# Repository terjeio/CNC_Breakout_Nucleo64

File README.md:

## CNC Breakout board for Nucleo-64 based development boards using ST morpho extension header

[grblHAL driver](https://github.com/grblHAL/STM32F4xx) support for [Nucleo F411RE](https://www.st.com/en/evaluation-tools/nucleo-f411re.html) and [Nucleo F446RE](https://www.st.com/en/evaluation-tools/nucleo-f446re.html) development boards.

**NOTE:** design files are in [KiCad 5](http://www.kicad.org/) format!

**Features:**

* Four layer board

* 4-axis motor support with separate enable for all axes.

* On-board sockets for Polulu \(A4998 and DRV8825\) or Trinamic \(TMC2130 or TMC5160 - SPI mode, TMC2209 - UART mode\) style motor driver modules.

* Opto-coupled limit and signal inputs (X, Y, Z, A, Probe, Reset/E-Stop, Door, Feed Hold and Cycle Start).

* Opto-coupled signal outputs \(Spindle on, Spindle direction, Flood, Mist, Aux0 and Aux1\).
Outputs are open drain \(ULN2003\) capable of draining 500mA, enough to drive most relays directly.

* Jumper selectable drive voltage for inputs and outputs, either 5V internally supplied or 5-30V externally supplied. 
If externally supplied inputs and outputs can be made galvanically isolated from the controller via jumper settings.

* 5V buffered PWM output for spindle speed control.

* Optional optocoupled DC spindle output, can be made galvanically isolated via jumper setting. External supply voltage limited to rating of filtering capacitor C7 (max. 30V).

* I2C port with jumper selectable drive voltage \(3.3V or 5V\). This is complemented with a 5V tolerant input pin that may be used as an interrupt source, eg. for the strobe signal from a I2C-based keypad.

* Two GPIO ports, with two pins each. One is unbuffered and can be used for serial communincation, eg. for MPG or VFD control. One is input only and has 5V tolerant pins.

* Optional on-board EEPROM/FRAM for persistent storage of settings.

* SPI based SD-card interface. If not in use some or all pins may be used as GPIO or as a generic SPI interface with one chip select line, depending on motor drivers used.

---

I have a number of _bare_ boards available:

* 1.0 \(preliminary version\): 7 pcs. These do not support Trinamic drivers in SPI/UART mode and has a couple of correctable routing errors in the spindle PWM -> spindle DC circuit. Price: shipping at cost.

* 1.0b: 2 pcs. Price: EUR 5/pcs + shipping at cost. These are missing a pullup resistor for the keypad strobe input - this _may_ affect operation of the keypad plugin. Easy to add externally.

These boards are gold plated \(ENIG finish\).

* 1.0c: \(current version\) Not yet available.

I do not plan to offer populated boards as either I have to solder them myself \(will be expensive\) or place an order for ready made boards \(with only SMD components soldered\).  
A redesign is likely required for ready made boards as some of the components may not be available from the standard selection offered by e.g. [JLPCB](https://jlcpcb.com/).

It would be great if someone would get populated boards made and offered for sale as I am currently not prepared to do that.

---

2021-08-22

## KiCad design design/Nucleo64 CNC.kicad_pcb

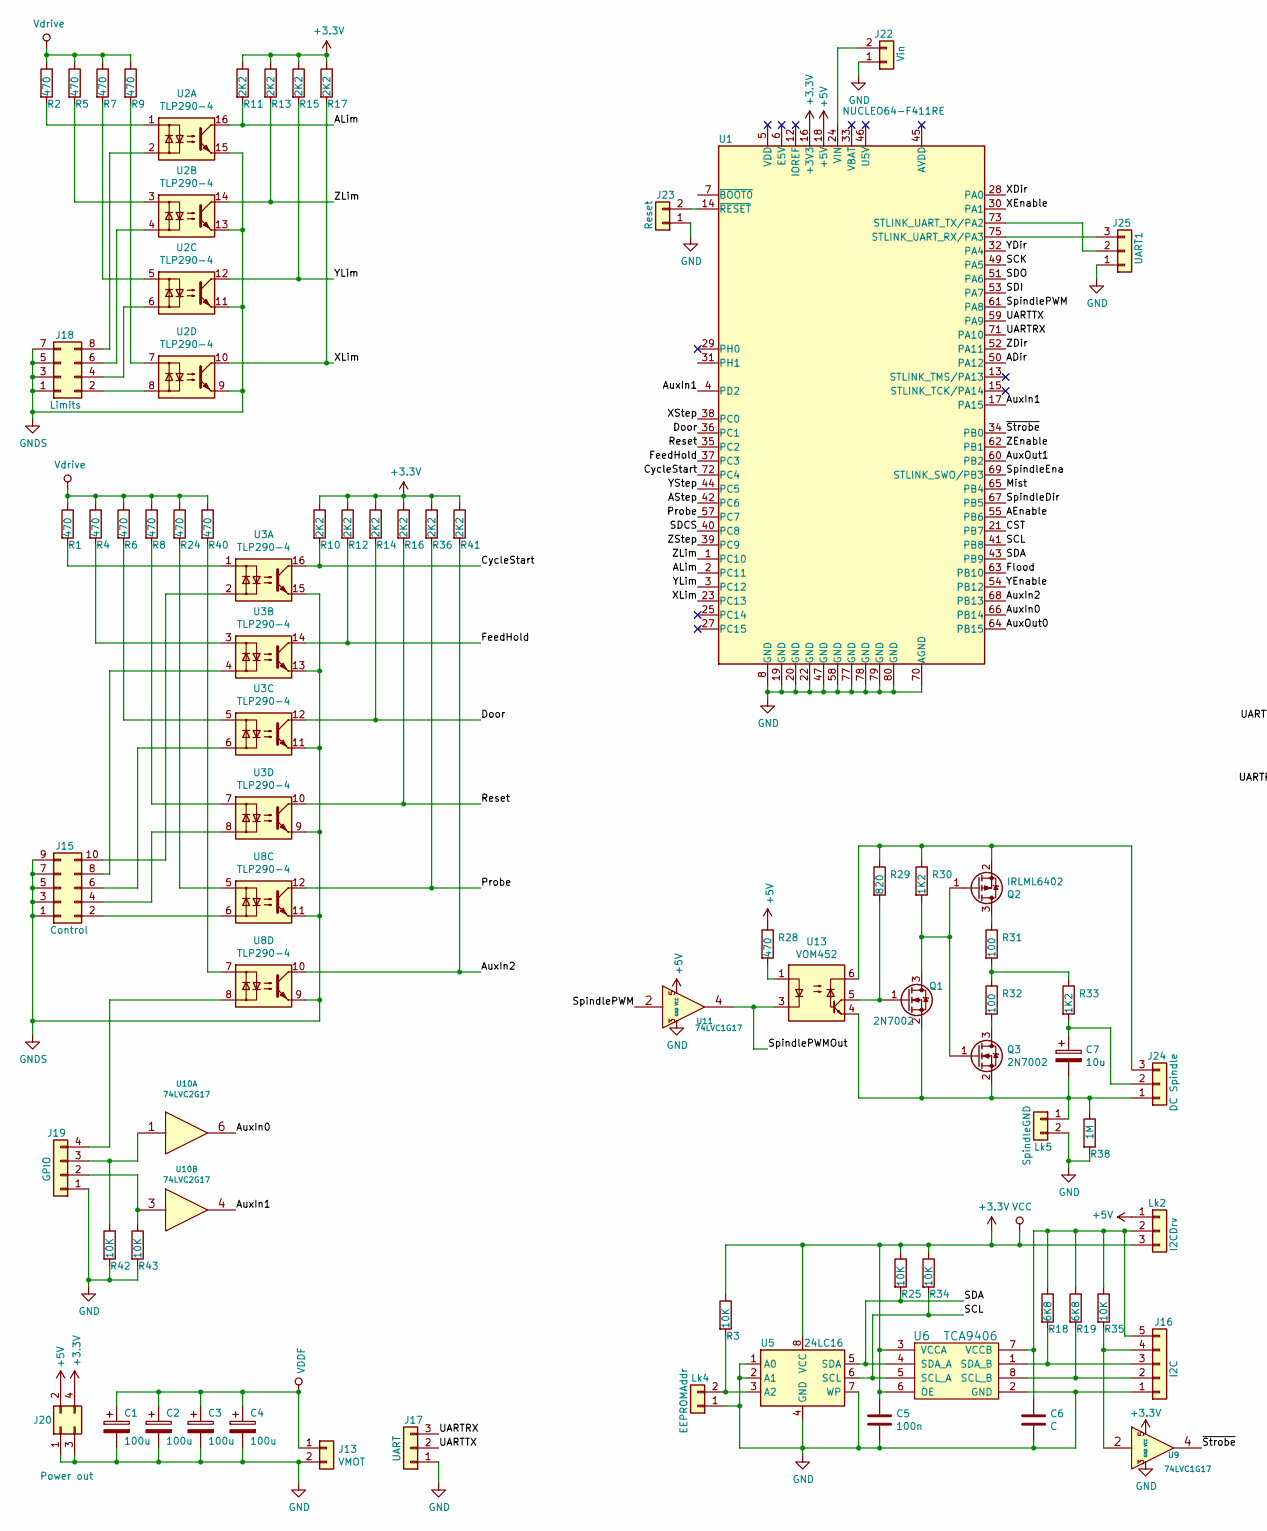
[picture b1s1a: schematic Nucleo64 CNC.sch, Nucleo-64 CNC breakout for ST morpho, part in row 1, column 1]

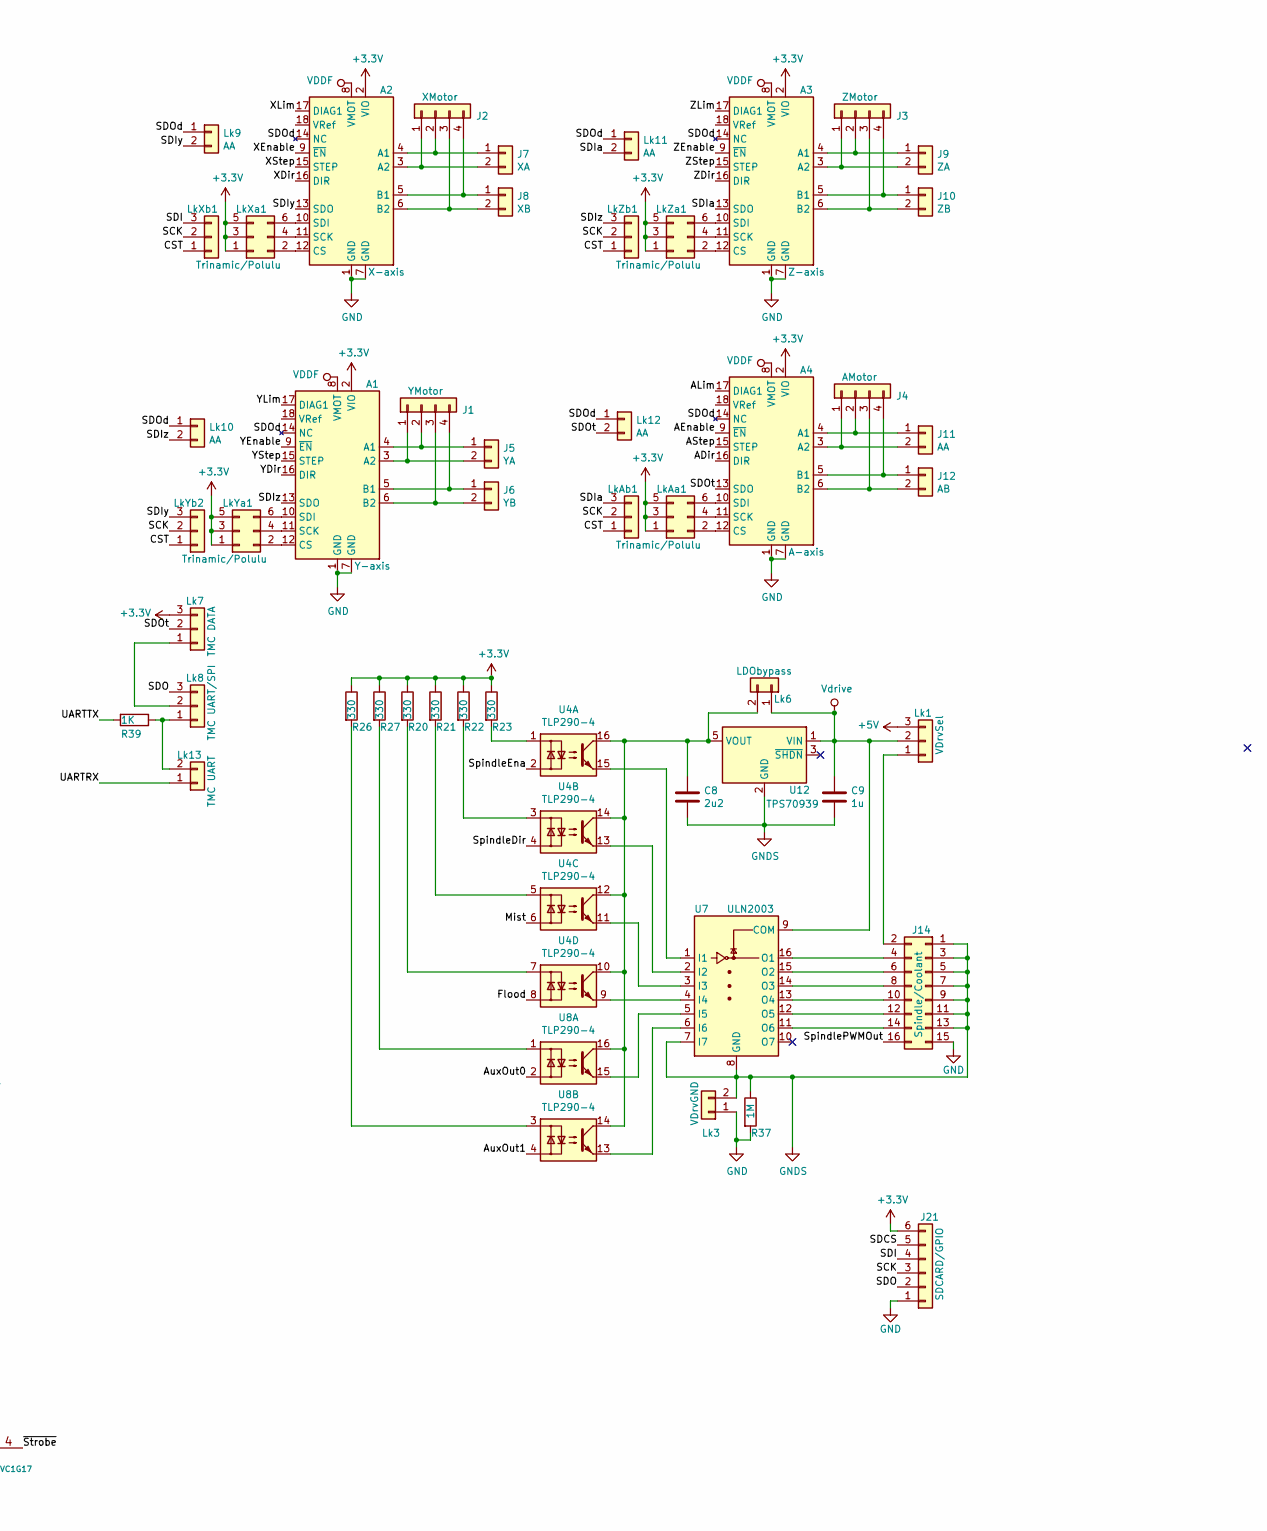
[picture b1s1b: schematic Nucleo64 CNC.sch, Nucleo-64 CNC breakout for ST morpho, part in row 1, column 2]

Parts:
A1: Y-axis; SilentStepStick_TMC2130
A2: X-axis; SilentStepStick_TMC2130
A3: Z-axis; SilentStepStick_TMC2130
A4: A-axis; SilentStepStick_TMC2130
C1, C2, C3, C4: 100u; CP_Radial_D8.0mm_P3.50mm
C5: 100n; C_0805_2012Metric
C6: C; C_0805_2012Metric
C7: 10u; CP_EIA-3216-10_Kemet-I
C8: 2u2; C_1206_3216Metric
C9: 1u; C_1206_3216Metric
J1: YMotor; PinHeader_1x04_P2.54mm_Vertical
J2: XMotor; PinHeader_1x04_P2.54mm_Vertical
J3: ZMotor; PinHeader_1x04_P2.54mm_Vertical
J4: AMotor; PinHeader_1x04_P2.54mm_Vertical
J5: YA; CONN_PWR_2P_3.5MM_CAMBLOCK
J6: YB; CONN_PWR_2P_3.5MM_CAMBLOCK
J7: XA; CONN_PWR_2P_3.5MM_CAMBLOCK
J8: XB; CONN_PWR_2P_3.5MM_CAMBLOCK
J9: ZA; CONN_PWR_2P_3.5MM_CAMBLOCK
J10: ZB; CONN_PWR_2P_3.5MM_CAMBLOCK
J11: AA; CONN_PWR_2P_3.5MM_CAMBLOCK
J12: AB; CONN_PWR_2P_3.5MM_CAMBLOCK
J13: VMOT; CONN_PWR_2P_3.5MM_CAMBLOCK
J14: Spindle/Coolant; PinHeader_2x08_P2.54mm_Vertical
J15: Control; PinHeader_2x05_P2.54mm_Vertical
J16: I2C; PinHeader_1x05_P2.54mm_Vertical
J17: UART; PinHeader_1x03_P2.54mm_Vertical
J18: Limits; PinHeader_2x04_P2.54mm_Vertical
J19: GPIO; PinHeader_1x04_P2.54mm_Vertical
J20: Power out; PinHeader_2x02_P2.54mm_Vertical
J21: SDCARD/GPIO; PinHeader_1x06_P2.54mm_Vertical
J22: Vin; PinHeader_1x02_P2.54mm_Vertical
J23: Reset; PinHeader_1x02_P2.54mm_Vertical
J24: DC Spindle; PinHeader_1x03_P2.54mm_Vertical
J25: UART1; PinHeader_1x03_P2.54mm_Vertical
Lk1: VDrvSel; PinHeader_1x03_P2.54mm_Vertical
Lk2: I2CDrv; PinHeader_1x03_P2.54mm_Vertical
Lk3: VDrvGND; PinHeader_1x02_P2.54mm_Vertical
Lk4: EEPROMAddr; SolderJumper-2_P1.3mm_Open_RoundedPad1.0x1.5mm
Lk5: SpindleGND; PinHeader_1x02_P2.54mm_Vertical
Lk6: LDObypass; SolderJumper-2_P1.3mm_Open_RoundedPad1.0x1.5mm
Lk7: TMC DATA; PinHeader_1x03_P2.54mm_Vertical
Lk8: TMC UART/SPI; PinHeader_1x03_P2.54mm_Vertical
Lk9, Lk10, Lk11, Lk12: AA; PinHeader_1x02_P2.54mm_Vertical
Lk13: TMC UART; PinHeader_1x02_P2.54mm_Vertical
LkAa1: Trinamic/Polulu; PinHeader_2x03_P2.54mm_Vertical
LkAb1: PinHeader_1x03_P2.54mm_Vertical
LkXa1: Trinamic/Polulu; PinHeader_2x03_P2.54mm_Vertical
LkXb1: PinHeader_1x03_P2.54mm_Vertical
LkYa1: Trinamic/Polulu; PinHeader_2x03_P2.54mm_Vertical
LkYb2: PinHeader_1x03_P2.54mm_Vertical
LkZa1: Trinamic/Polulu; PinHeader_2x03_P2.54mm_Vertical
LkZb1: PinHeader_1x03_P2.54mm_Vertical
Q1, Q3: 2N7002; SOT-23
Q2: IRLML6402; SOT-23
R1, R2, R4, R5, R6, R7, R8, R9, R24, R28, R40: 470; R_0805_2012Metric
R3, R25, R34, R35, R42, R43: 10K; R_0805_2012Metric
R10, R11, R12, R13, R14, R15, R16, R17, R36, R41: 2K2; R_0805_2012Metric
R18, R19: 6K8; R_0805_2012Metric
R20, R21, R22, R23, R26, R27: 330; R_0805_2012Metric
R29: 820; R_0805_2012Metric
R30, R33: 1K2; R_0805_2012Metric
R31, R32: 100; R_0805_2012Metric
R37, R38: 1M; R_0805_2012Metric
R39: 1K; R_0805_2012Metric
U1: NUCLEO64-F411RE; ST_Morpho_Connector_64_STLink
U2, U3, U4, U8: TLP290-4; SOP-16_4.55x10.3mm_P1.27mm
U5: 24LC16; SOIC-8_3.9x4.9mm_P1.27mm
U6: TCA9406; SSOP-8_2.95x2.8mm_P0.65mm
U7: ULN2003; SOIC-16_3.9x9.9mm_P1.27mm
U9, U11: 74LVC1G17; SOT-353_SC-70-5
U10: 74LVC2G17; SOT-23-6
U12: TPS70939; SOT-23-5
U13: VOM452; MFSOP6-5_4.4x3.6mm_P1.27mm

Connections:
+3V3: A1.2 (VIO), A2.2 (VIO), A3.2 (VIO), A4.2 (VIO), C5.1, J20.4, J21.6, Lk2.3, Lk7.3, LkAa1.1, LkAa1.3, LkAa1.5, LkXa1.1, LkXa1.3, LkXa1.5, LkYa1.1, LkYa1.3, LkYa1.5, LkZa1.1, LkZa1.3, LkZa1.5, R3.1, R10.1, R11.1, R12.1, R13.1, R14.1, R15.1, R16.1, R17.1, R20.1, R21.1, R22.1, R23.1, R25.1, R26.1, R27.1, R34.1, R36.1, R41.1, U1.16 (+3V3), U5.8 (VCC), U6.3 (VCCA), U6.6 (OE), U9.5 (VCC), U10.5 (VCC)
+5V: J20.2, Lk1.3, Lk2.1, R28.1, U1.18 (+5V), U11.5 (VCC)
/ADir: A4.16 (DIR), U1.50 (PA12)
/AEnable: A4.9 (~EN), U1.55 (PB6)
/ALim: A4.17 (DIAG1), R11.2, U1.2 (PC11), U2.16
/AStep: A4.15 (STEP), U1.42 (PC6)
/AuxIn0: U1.66 (PB14), U10.6
/AuxIn1: U1.4 (PD2), U1.17 (PA15), U10.4
/AuxIn2: R41.2, U1.68 (PB13), U8.10
/AuxOut0: U1.64 (PB15), U8.2
/AuxOut1: U1.60 (PB2), U8.4
/CST: LkAb1.1, LkXb1.1, LkYb2.1, LkZb1.1, U1.21 (PB7)
/CycleStart: R10.2, U1.72 (PC4), U3.16
/Door: R14.2, U1.36 (PC1), U3.12
/FeedHold: R12.2, U1.37 (PC3), U3.14
/Flood: U1.63 (PB10), U4.8
/Mist: U1.65 (PB4), U4.6
/Probe: R36.2, U1.57 (PC7), U8.12
/Reset: R16.2, U1.35 (PC2), U3.10
/SCK: J21.3, LkAb1.2, LkXb1.2, LkYb2.2, LkZb1.2, U1.49 (PA5)
/SCL: R34.2, U1.41 (PB8), U5.6 (SCL), U6.5 (SCL_A)
/SDA: R25.2, U1.43 (PB9), U5.5 (SDA), U6.4 (SDA_A)
/SDCS: J21.5, U1.40 (PC8)
/SDI: J21.4, LkXb1.3, U1.53 (PA7)
/SDIa: A3.13 (SDO), Lk11.2, LkAb1.3
/SDIy: A2.13 (SDO), Lk9.2, LkYb2.3
/SDIz: A1.13 (SDO), Lk10.2, LkZb1.3
/SDO: J21.2, Lk8.3, U1.51 (PA6)
/SDOd: A1.14 (NC), A2.14 (NC), A3.14 (NC), A4.14 (NC), Lk9.1, Lk10.1, Lk11.1, Lk12.1
/SDOt: A4.13 (SDO), Lk7.2, Lk12.2
/SpindleDir: U1.67 (PB5), U4.4
/SpindleEna: U1.69 (STLINK_SWO/PB3), U4.2
/SpindlePWM: U1.61 (PA8), U11.2
/SpindlePWMOut: J14.16, U11.4, U13.3 (C)
/UARTRX: J17.3, Lk13.1, U1.71 (PA10)
/UARTTX: J17.2, R39.2, U1.59 (PA9)
/XDir: A2.16 (DIR), U1.28 (PA0)
/XEnable: A2.9 (~EN), U1.30 (PA1)
/XLim: A2.17 (DIAG1), R17.2, U1.23 (PC13), U2.10
/XStep: A2.15 (STEP), U1.38 (PC0)
/YDir: A1.16 (DIR), U1.32 (PA4)
/YEnable: A1.9 (~EN), U1.54 (PB12)
/YLim: A1.17 (DIAG1), R15.2, U1.3 (PC12), U2.12
/YStep: A1.15 (STEP), U1.44 (PC5)
/ZDir: A3.16 (DIR), U1.52 (PA11)
/ZEnable: A3.9 (~EN), U1.62 (PB1)
/ZLim: A3.17 (DIAG1), R13.2, U1.1 (PC10), U2.14
/ZStep: A3.15 (STEP), U1.39 (PC9)
/~Strobe: U1.34 (PB0), U9.4
GND: A1.1 (GND), A1.7 (GND), A2.1 (GND), A2.7 (GND), A3.1 (GND), A3.7 (GND), A4.1 (GND), A4.7 (GND), C1.2, C2.2, C3.2, C4.2, C5.2, C6.2, J13.2, J14.15, J16.1, J17.1, J19.1, J20.1, J20.3, J21.1, J22.1, J23.1, J25.1, Lk3.1, Lk4.1, Lk5.2, R37.2, R38.2, R42.2, R43.2, U1.8 (GND), U1.19 (GND), U1.20 (GND), U1.22 (GND), U1.47 (GND), U1.58 (GND), U1.70 (AGND), U1.77 (GND), U1.78 (GND), U1.79 (GND), U1.80 (GND), U5.1 (A0), U5.2 (A1), U5.4 (GND), U5.7 (WP), U6.2 (GND), U9.3 (GND), U10.2 (GND), U11.3 (GND)
GNDS: C8.2, C9.2, J14.1, J14.3, J14.5, J14.7, J14.9, J14.11, J14.13, J15.1, J15.3, J15.5, J15.7, J15.9, J18.1, J18.3, J18.5, J18.7, Lk3.2, R37.1, U2.9, U2.11, U2.13, U2.15, U3.9, U3.11, U3.13, U3.15, U7.7 (I7), U7.8 (GND), U8.9, U8.11, U12.2 (GND)
unnamed: A1.3 (A2), J1.1, J5.2
unnamed: A1.4 (A1), J1.2, J5.1
unnamed: A1.5 (B1), J1.4, J6.1
unnamed: A1.6 (B2), J1.3, J6.2
unnamed: A1.10 (SDI), LkYa1.6
unnamed: A1.11 (SCK), LkYa1.4
unnamed: A1.12 (CS), LkYa1.2
unnamed: A2.3 (A2), J2.1, J7.2
unnamed: A2.4 (A1), J2.2, J7.1
unnamed: A2.5 (B1), J2.4, J8.1
unnamed: A2.6 (B2), J2.3, J8.2
unnamed: A2.10 (SDI), LkXa1.6
unnamed: A2.11 (SCK), LkXa1.4
unnamed: A2.12 (CS), LkXa1.2
unnamed: A3.3 (A2), J3.1, J9.2
unnamed: A3.4 (A1), J3.2, J9.1
unnamed: A3.5 (B1), J3.4, J10.1
unnamed: A3.6 (B2), J3.3, J10.2
unnamed: A3.10 (SDI), LkZa1.6
unnamed: A3.11 (SCK), LkZa1.4
unnamed: A3.12 (CS), LkZa1.2
unnamed: A4.3 (A2), J4.1, J11.2
unnamed: A4.4 (A1), J4.2, J11.1
unnamed: A4.5 (B1), J4.4, J12.1
unnamed: A4.6 (B2), J4.3, J12.2
unnamed: A4.10 (SDI), LkAa1.6
unnamed: A4.11 (SCK), LkAa1.4
unnamed: A4.12 (CS), LkAa1.2
unnamed: C6.1, J16.5, Lk2.2, R18.1, R19.1, R35.1, U6.7 (VCCB)
unnamed: C7.1, J24.2, R33.2
unnamed: C7.2, J24.1, Lk5.1, Q1.2 (S), Q3.2 (S), R38.1, U13.4 (GND)
unnamed: C8.1, Lk6.2, U4.10, U4.12, U4.14, U4.16, U8.14, U8.16, U12.5 (VOUT)
unnamed: J14.2, Lk1.1
unnamed: J14.4, U7.16 (O1)
unnamed: J14.6, U7.15 (O2)
unnamed: J14.8, U7.14 (O3)
unnamed: J14.10, U7.13 (O4)
unnamed: J14.12, U7.12 (O5)
unnamed: J14.14, U7.11 (O6)
unnamed: J15.2, U8.6
unnamed: J15.4, U3.8
unnamed: J15.6, U3.6
unnamed: J15.8, U3.4
unnamed: J15.10, U3.2
unnamed: J16.2, R19.2, U6.8 (SCL_B)
unnamed: J16.3, R18.2, U6.1 (SDA_B)
unnamed: J16.4, R35.2, U9.2
unnamed: J18.2, U2.8
unnamed: J18.4, U2.6
unnamed: J18.6, U2.4
unnamed: J18.8, U2.2
unnamed: J19.2, R43.1, U10.3
unnamed: J19.3, R42.1, U10.1
unnamed: J19.4, U8.8
unnamed: J22.2, U1.24 (VIN)
unnamed: J23.2, U1.14 (~RESET)
unnamed: J24.3, Q2.2 (S), R29.1, R30.1, U13.6 (VCC)
unnamed: J25.2, U1.73 (STLINK_UART_TX/PA2)
unnamed: J25.3, U1.75 (STLINK_UART_RX/PA3)
unnamed: Lk4.2, R3.2, U5.3 (A2)
unnamed: Lk7.1, Lk8.2
unnamed: Lk8.1, Lk13.2, R39.1
unnamed: Q1.1 (G), R29.2, U13.5 (VO)
unnamed: Q1.3 (D), Q2.1 (G), Q3.1 (G), R30.2
unnamed: Q2.3 (D), R31.1
unnamed: Q3.3 (D), R32.2
unnamed: R1.2, U3.1
unnamed: R2.2, U2.1
unnamed: R4.2, U3.3
unnamed: R5.2, U2.3
unnamed: R6.2, U3.5
unnamed: R7.2, U2.5
unnamed: R8.2, U3.7
unnamed: R9.2, U2.7
unnamed: R20.2, U4.7
unnamed: R21.2, U4.5
unnamed: R22.2, U4.3
unnamed: R23.2, U4.1
unnamed: R24.2, U8.5
unnamed: R26.2, U8.3
unnamed: R27.2, U8.1
unnamed: R28.2, U13.1 (A)
unnamed: R31.2, R32.1, R33.1
unnamed: R40.2, U8.7
unnamed: U4.9, U7.4 (I4)
unnamed: U4.11, U7.3 (I3)
unnamed: U4.13, U7.2 (I2)
unnamed: U4.15, U7.1 (I1)
unnamed: U7.5 (I5), U8.15
unnamed: U7.6 (I6), U8.13
VDDF: A1.8 (VMOT), A2.8 (VMOT), A3.8 (VMOT), A4.8 (VMOT), C1.1, C2.1, C3.1, C4.1, J13.1
Vdrive: C9.1, Lk1.2, Lk6.1, R1.1, R2.1, R4.1, R5.1, R6.1, R7.1, R8.1, R9.1, R24.1, R40.1, U7.9 (COM), U12.1 (VIN)

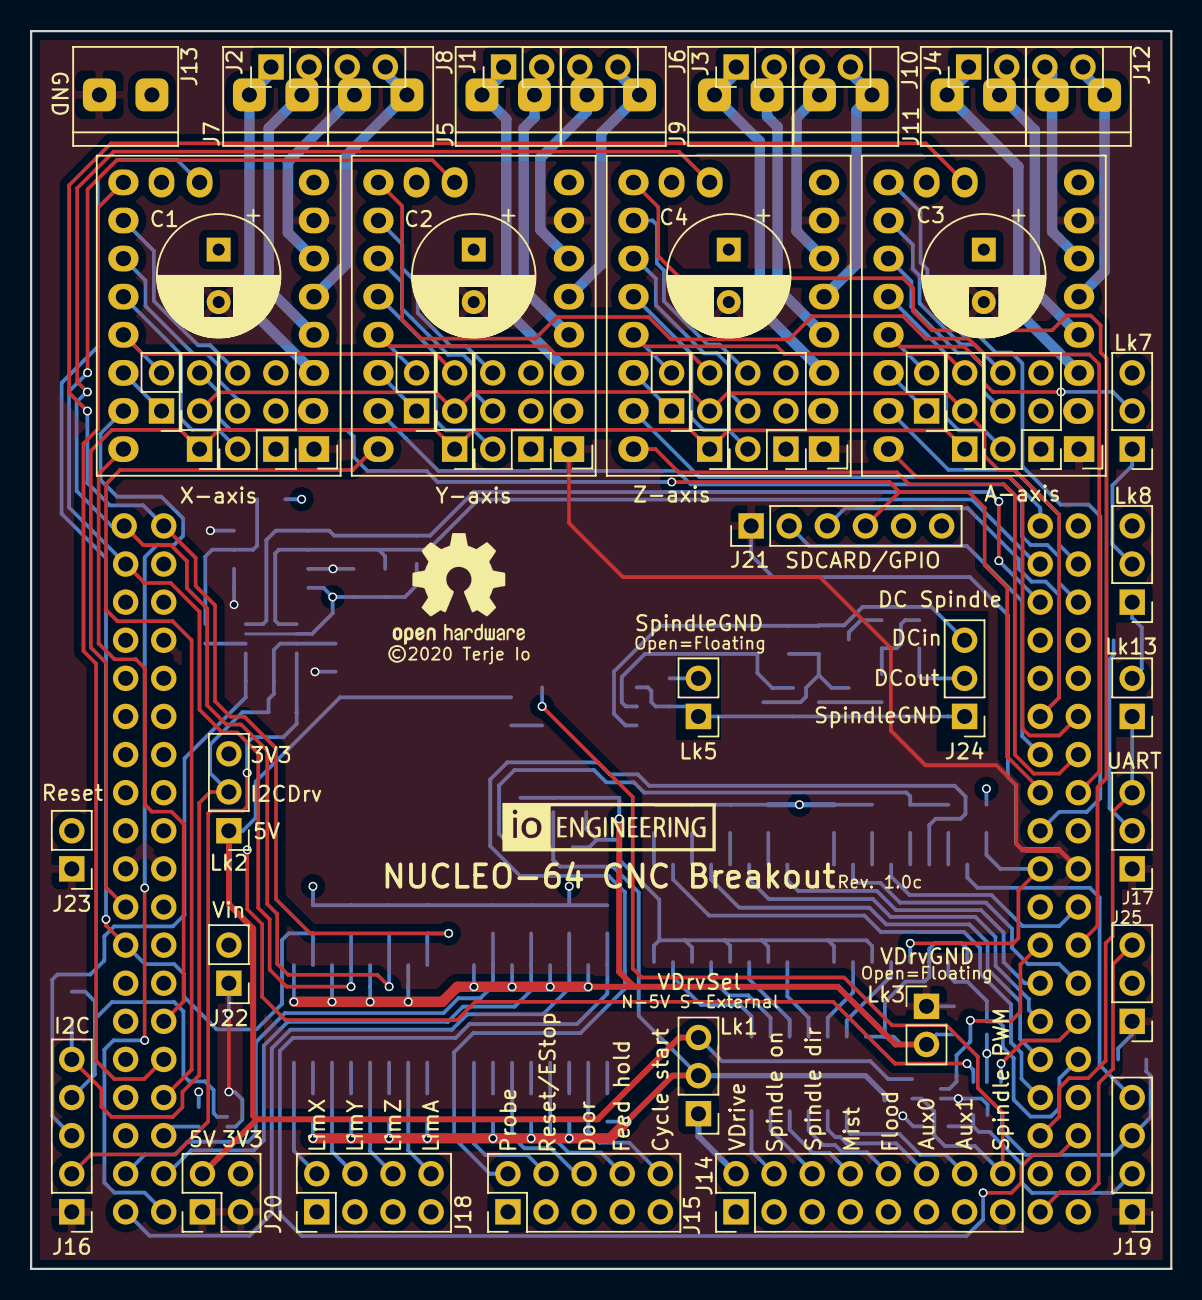
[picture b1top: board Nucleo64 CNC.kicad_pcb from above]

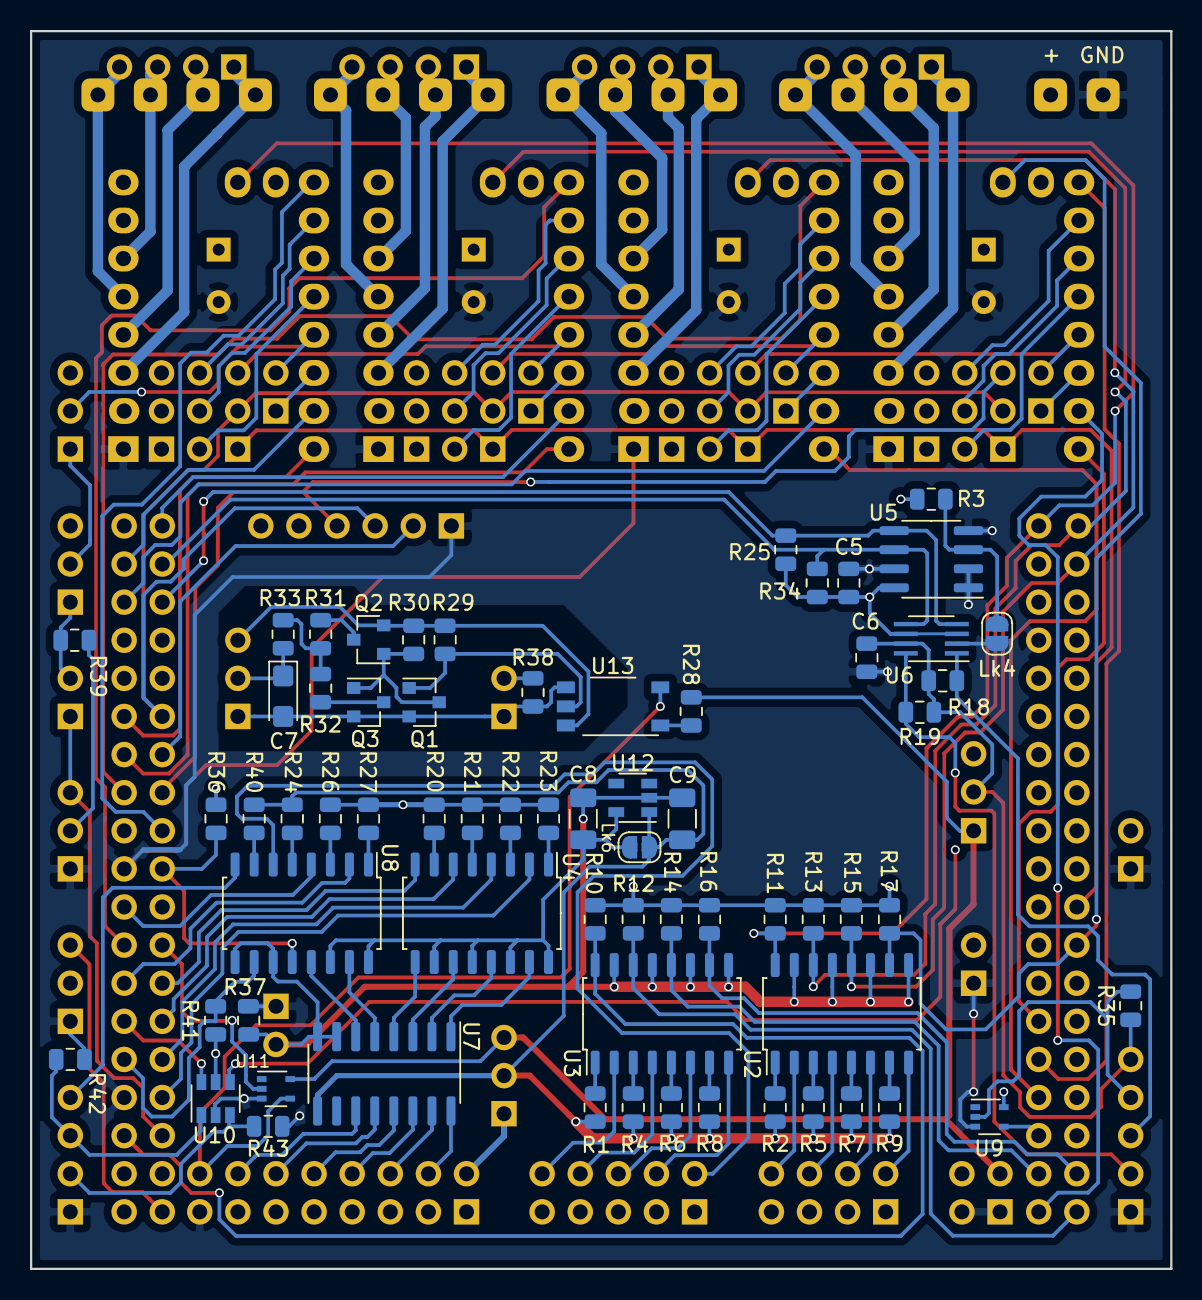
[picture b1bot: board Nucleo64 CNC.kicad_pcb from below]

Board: 4 copper layers, 76.0 x 82.5 mm, 118 parts (65 on the bottom side), 143 nets.

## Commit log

2020-11-22 Updated to version sent for small prototype batch
    Design and board map file to be verified with this batch.
2021-08-22 Updated to v1.0c
2021-10-21 Updated kicad link
2023-03-12 Added board configs

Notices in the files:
design/Nucleo64 CNC.kicad_pcb:
Licensed under CERN OHL v.1.2 or later
©2020 Terje Io
